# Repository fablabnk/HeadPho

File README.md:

Footprint for NJM4556AV-TE1 can be found here: https://componentsearchengine.com/part-view/NJM4556AV-TE1/New%20Japan%20Radio

# Todo

TODO: take power footprint out of stereo pot footprint (this overlap isn't good!)
DONE: double check schematic against original
TODO: Convert panel holes to NPTH to avoid maximum plated hole size warning (although we won't sent these to fab, so doesn't really matter)

# Inspiration

https://llllllll.co/t/exits-a-4hp-mixer-line-headphone-output-module/52221
https://github.com/forestcaver/Analog-Voice/tree/master/AJH_Headphone_Amp - not kicad
https://www.ericasynths.lv/shop/diy-kits-1/edu-diy-output/
https://busycircuits.com/alm019/
https://nwavguy.blogspot.com/2011/07/o2-headphone-amp.html
https://github.com/russellmcc/eurorack_headphones - kicad
https://github.com/ramphands/Exits - kicad, SMT, op amp available on ali but not common
https://github.com/wntrblm/Speak_to_Me - kicad, headphone amp with inbuilt speaker
https://github.com/tkilla64/eurorack/tree/main/output

# Features

- left and right mono jack 3.5mm inputs - mono sums over when only left plugged
- stereo volume pot
- L and R mono jack 3.5mm outputs (line level)
- stereo 3.5mm jack output

# Circuit explanation

- Audio comes in on 3.5mm mono jacks (L and R)
- The switched input of the R jack takes audio from the L jack, so that when R is not plugged in we get a copy of the L signal in the R output
- Audio level is dropped to line level for L and R channels by two LME49720 audio op amps
- Audio goes out to L and R 3.5mm line level jacks
- A stereo potentiometer attentuates the line level signal for both channels equally
- Two NJM4556 chips drive the headphones
- Audio op amps are needed (LME49720) and an amplifier chip capable of driving (low impedence) headphones

# How It Will Be Used in Our Rack

- two of these will be installed in our rack
- the buff mult can duplicate the final output signal
- we can send this independently to two separate headphone amps

# Notes

- The large amount of 100n decoupling caps is because we need 1 pair per chip, which on the PCB should be placed as close to chip power pins as possible
- I removed the ADP0204 dip switch in the original circuit
    - when switched on, engages an extra 100K resistor between input and output of the opamp on each channel
    - I guess to further attentuate the input signal perhaps to allow for line-level input
    - I will just experiment with different resistor values here instead
- is there any THT alternative to NJM4556AV-TE1? Yes NJM4556AD DIP with same pinout
- symbol pins 7 and 8 on dual pot are just mount points

# Switched plugs explained simply

- Switched plugs have a switch contact/pin
- When there is no plug inserted into the jack the tip contact is touching the switch contact
- This creates a closed circuit between the input signal and the output path through the switch contact
- When a plug is inserted into the jack the signal now flows through the plug instead of the switch contact
- In the case of my headphone amp, I want L input to connect (normal over) to the R when no plug is inserted in the R
- This means that the tip output of the L jack is connected to the switch contact of the R jack

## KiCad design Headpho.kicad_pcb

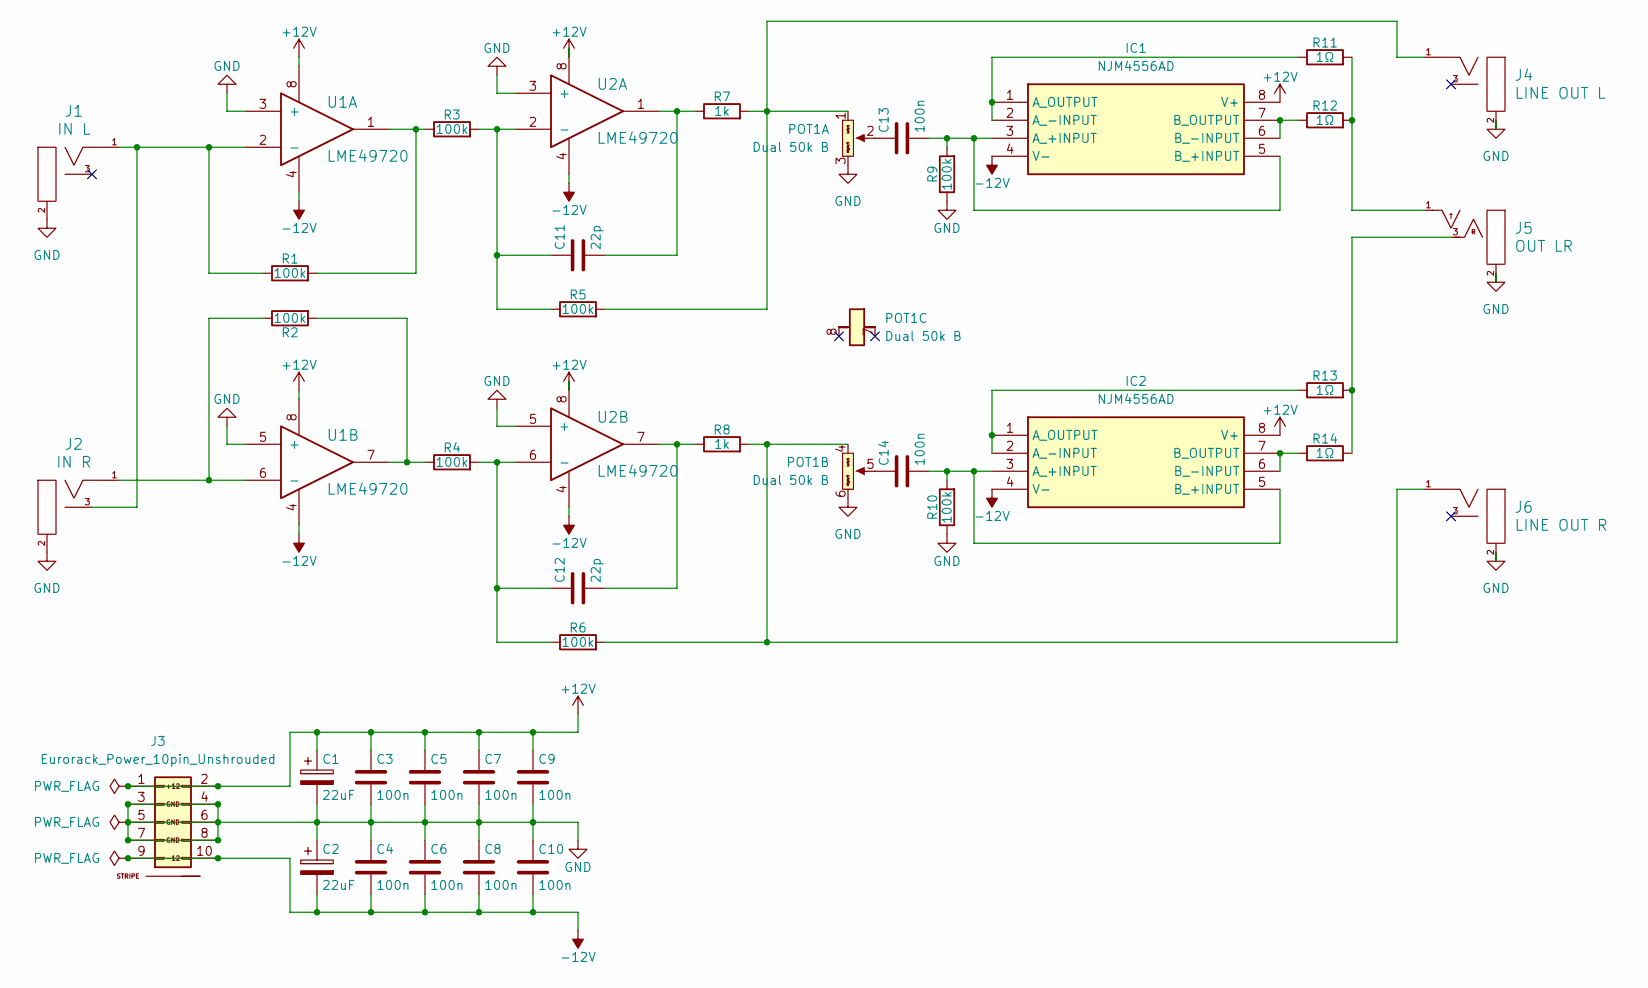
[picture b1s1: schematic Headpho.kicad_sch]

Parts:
C1, C2: 22uF; CP_Radial_D4.0mm_P2.00mm
C3, C4, C5, C6, C7, C8, C9, C10, C13, C14: 100n; C_Disc_D3.0mm_W1.6mm_P2.50mm
C11, C12: 22p; C_Disc_D3.0mm_W1.6mm_P2.50mm
IC1, IC2: NJM4556AD; DIP-8_W7.62mm_Socket; Manufacturer_Part_Number NJM4556AV-TE1; Mouser Part Number 513-NJM4556AV-TE1
J1: IN L; EighthInch_PJ398SM_3mmNPTH; Part Number WQP-WQP518MA
J2: IN R; EighthInch_PJ398SM_3mmNPTH; Part Number WQP-WQP518MA
J3: Eurorack_Power_10pin_Unshrouded; IDC-Header_2x05_P2.54mm_Vertical_Euro_Power_Striped_Thicker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; Part Number 1-1002FBV0T
J4: LINE OUT L; EighthInch_PJ398SM_3mmNPTH; Part Number WQP-WQP518MA
J5: OUT LR; EighthInch_Stereo_PJ366ST_NPTH; Part Number WQP-WQP518MA
J6: LINE OUT R; EighthInch_PJ398SM_3mmNPTH; Part Number WQP-WQP518MA
POT1: 9mm_Dual_50k_DShaft_DualRow; Dual_9mm_Potentiometer_50K_RK1114GH; Part Number 9M2V5BNB-D-15F-B50K-19WE
R1, R2, R3, R4, R5, R6, R9, R10: 100k; R_Axial_DIN0204_L3.6mm_D1.6mm_P1.90mm_Vertical
R7, R8: 1k; R_Axial_DIN0204_L3.6mm_D1.6mm_P1.90mm_Vertical
R11, R12, R13, R14: 1Ω; R_Axial_DIN0204_L3.6mm_D1.6mm_P1.90mm_Vertical
U1, U2: LME49720; DIP-8_W7.62mm_Socket

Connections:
+12V: C1.1, C3.1, C5.1, C7.1, C9.1, IC1.8 (V+), IC2.8 (V+), J3.1 (+12V), J3.2 (+12V), U1.8, U2.8
-12V: C2.2, C4.2, C6.2, C8.2, C10.2, IC1.4 (V-), IC2.4 (V-), J3.9 (-12V), J3.10 (-12V), U1.4, U2.4
GND: C1.2, C2.1, C3.2, C4.1, C5.2, C6.1, C7.2, C8.1, C9.2, C10.1, J1.2 (SHEILD), J2.2 (SHEILD), J3.3 (GND), J3.4 (GND), J3.5 (GND), J3.6 (GND), J3.7 (GND), J3.8 (GND), J4.2 (SHEILD), J5.2 (SHEILD), J6.2 (SHEILD), POT1.3 (Right), POT1.6 (Right), R9.1, R10.1, U1.3 (+), U1.5 (+), U2.3 (+), U2.5 (+)
unnamed: C11.2, R7.1, U2.1
unnamed: C12.2, R8.1, U2.7
unnamed: C13.2, IC1.3 (A_+INPUT), IC1.5 (B_+INPUT), R9.2
unnamed: IC1.1 (A_OUTPUT), IC1.2 (A_-INPUT), R11.1
unnamed: IC1.6 (B_-INPUT), IC1.7 (B_OUTPUT), R12.1
unnamed: C14.2, IC2.3 (A_+INPUT), IC2.5 (B_+INPUT), R10.2
unnamed: IC2.1 (A_OUTPUT), IC2.2 (A_-INPUT), R13.1
unnamed: IC2.6 (B_-INPUT), IC2.7 (B_OUTPUT), R14.1
unnamed: J1.1 (SIG), J2.3 (SW), R1.1, U1.2 (-)
unnamed: J2.1 (SIG), R2.1, U1.6 (-)
unnamed: J4.1 (SIG), POT1.1 (Left), R5.2, R7.2
unnamed: J5.1 (SIG), R11.2, R12.2
unnamed: J5.3 (SW), R13.2, R14.2
unnamed: J6.1 (SIG), POT1.4 (Left), R6.2, R8.2
unnamed: C13.1, POT1.2 (Center)
unnamed: C14.1, POT1.5 (Center)
unnamed: R1.2, R3.1, U1.1
unnamed: R2.2, R4.1, U1.7
unnamed: C11.1, R3.2, R5.1, U2.2 (-)
unnamed: C12.1, R4.2, R6.1, U2.6 (-)

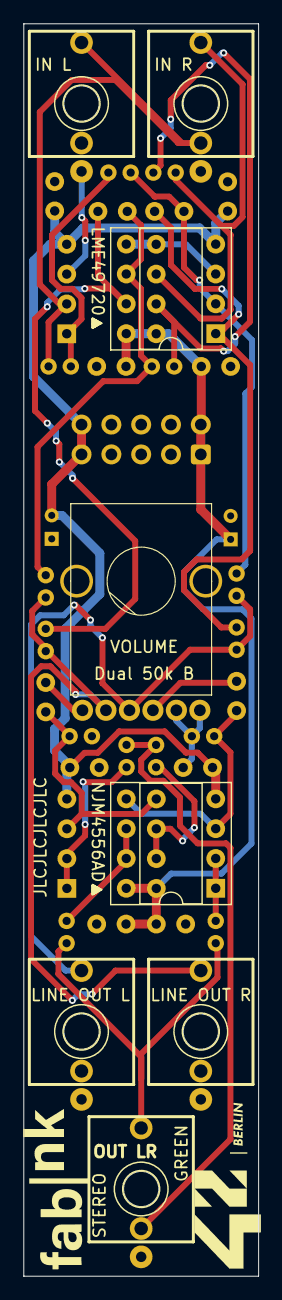
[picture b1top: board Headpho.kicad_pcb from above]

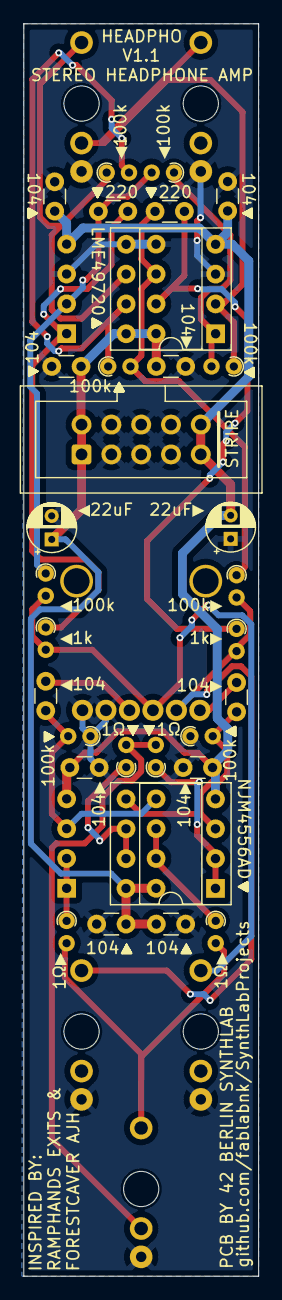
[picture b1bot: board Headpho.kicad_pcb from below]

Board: 2 copper layers, 20.0 x 106.7 mm, 39 parts (31 on the bottom side), 23 nets.

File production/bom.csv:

Designator,Footprint,Quantity,Value,LCSC Part #
"C1, C2",CP_Radial_D4.0mm_P2.00mm,2,22uF,
"C10, C13, C14, C3, C4, C5, C6, C7, C8, C9",C_Disc_D3.0mm_W1.6mm_P2.50mm,10,100n,
"C11, C12",C_Disc_D3.0mm_W1.6mm_P2.50mm,2,22p,
"IC1, IC2",DIP-8_W7.62mm_Socket,2,NJM4556AD,
J1,EighthInch_PJ398SM_3mmNPTH,1,IN L,
J2,EighthInch_PJ398SM_3mmNPTH,1,IN R,
J3,IDC-Header_2x05_P2.54mm_Vertical_Euro_Power_Striped_ThickerText,1,Eurorack_Power_10pin_Unshrouded,
J4,EighthInch_PJ398SM_3mmNPTH,1,LINE OUT L,
J5,EighthInch_Stereo_PJ366ST_NPTH,1,OUT LR,
J6,EighthInch_PJ398SM_3mmNPTH,1,LINE OUT R,
POT1,Dual_9mm_Potentiometer_50K_RK1114GH,1,9mm_Dual_50k_DShaft_DualRow,
"R1, R10, R2, R3, R4, R5, R6, R9",R_Axial_DIN0204_L3.6mm_D1.6mm_P1.90mm_Vertical,8,100k,
"R11, R12, R13, R14",R_Axial_DIN0204_L3.6mm_D1.6mm_P1.90mm_Vertical,4,1Ω,
"R7, R8",R_Axial_DIN0204_L3.6mm_D1.6mm_P1.90mm_Vertical,2,1k,
"U1, U2",DIP-8_W7.62mm_Socket,2,LME49720,

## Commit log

2024-07-31 layed out, routed and completed silkscreen corrections
2024-08-13 v1.0 almost ready for production
2024-08-15 v1.0 ready for production - fixed some minor silkscreening issues such as adding arrows
2024-08-15 shrunk height of board outline to pcb height not panel height
2024-09-15 added BuildNotes.md. Removed production folder
2024-09-22 v1.1 ready for final check
2024-12-01 updating after Dmitri's changes
2025-01-09 added production files
2025-01-11 fixed silkscreening issues before sending for new boards
